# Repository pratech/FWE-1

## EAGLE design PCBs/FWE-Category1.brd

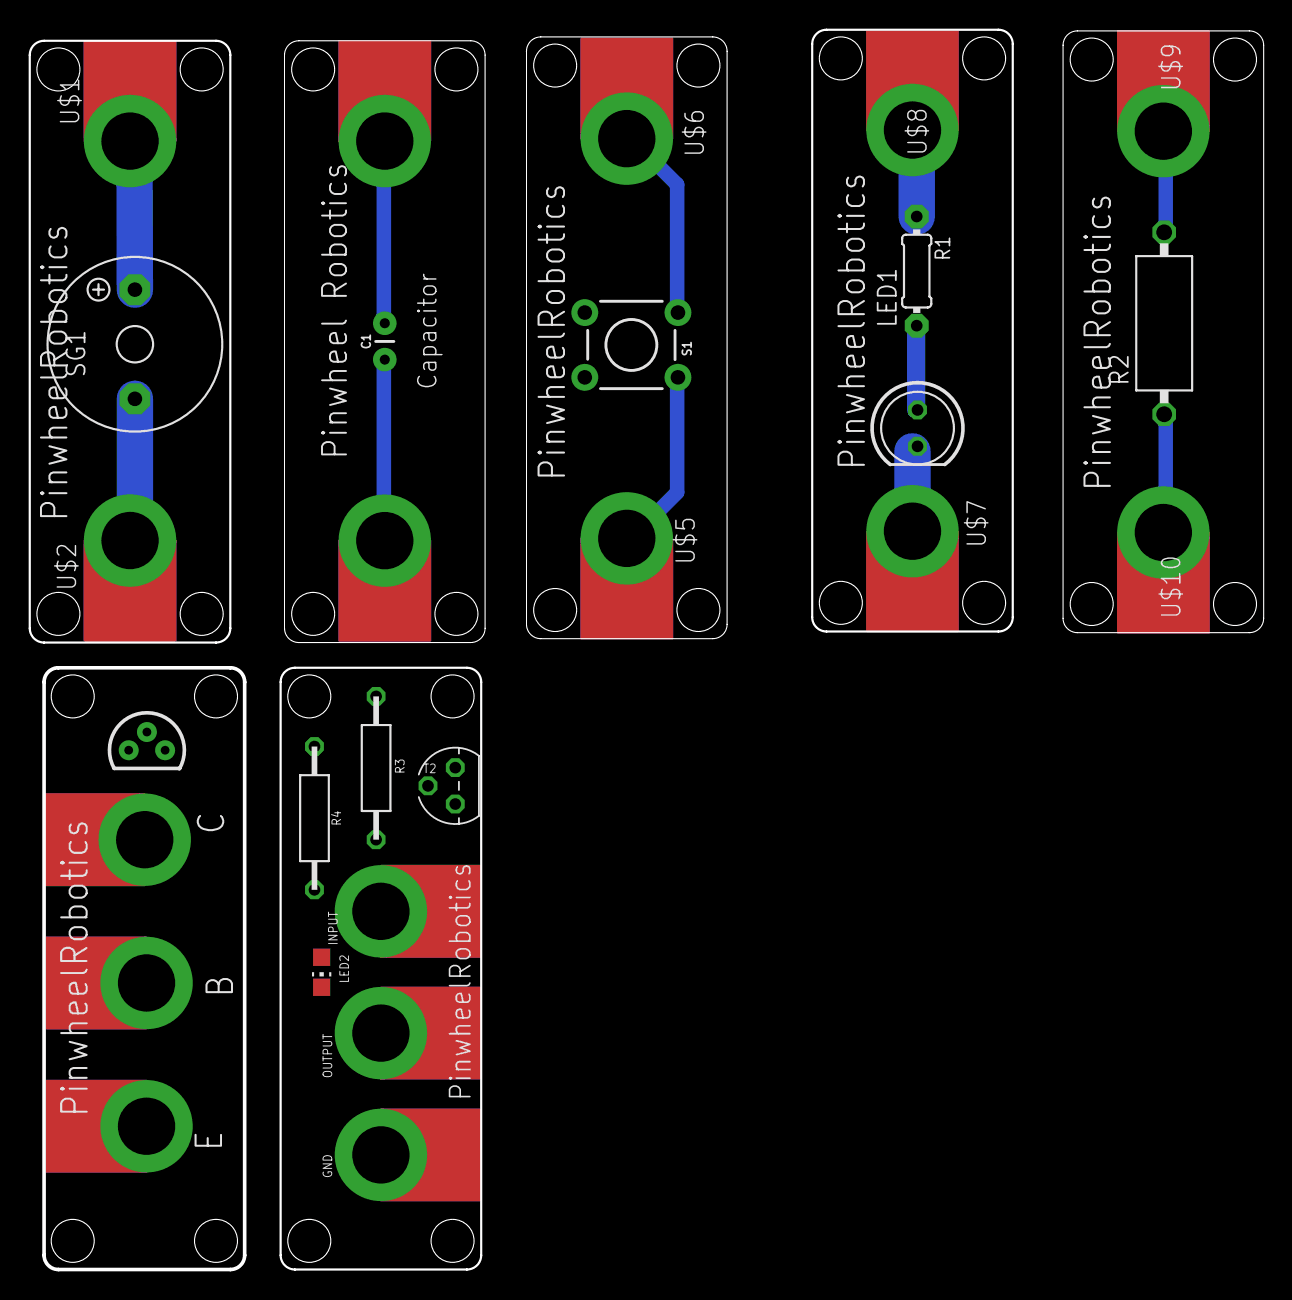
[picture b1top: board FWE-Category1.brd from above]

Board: 2 copper layers, 86.1 x 86.5 mm, 27 parts (0 on the bottom side), 19 nets.

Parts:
C1: 22pF; CAP-PTH-2.54
GND: MICROBIT_PAD
INPUT: MICROBIT_PAD
LED1: LED5MM
LED2: CHIP-LED0805
OUTPUT: MICROBIT_PAD
R1: 0204/7
R2: VMTB60
R3, R4: R0207/10
S1: MOMENTARY-SWITCH-SPST-PTH-6.0MM; TACTILE_SWITCH_PTH_6.0MM
SG1: F/TMB
T1: BC547N; TO92
T2: 2N3904; TO92
U$1, U$2, U$3, U$4, U$5, U$6, U$7, U$8, U$9, U$10, U$11, U$12, U$13: MICROBIT_PAD

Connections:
5V: INPUT.PAD, R3.1, R4.2
GND: GND.PAD, T2.3
unnamed: SG1.+, U$1.PAD
unnamed: SG1.-, U$2.PAD
unnamed: C1.1, U$4.PAD
unnamed: C1.2, U$3.PAD
unnamed: S1.1, U$5.PAD
unnamed: S1.3, U$6.PAD
unnamed: LED1.K, U$7.PAD
unnamed: LED1.A, R1.2
unnamed: R1.1, U$8.PAD
unnamed: R2.1, U$10.PAD
unnamed: R2.2, U$9.PAD
unnamed: T1.1, U$13.PAD
unnamed: T1.3, U$11.PAD
unnamed: LED2.A, R4.1
unnamed: LED2.C, OUTPUT.PAD, T2.1
unnamed: R3.2, T2.2
T1: T1.2, U$12.PAD

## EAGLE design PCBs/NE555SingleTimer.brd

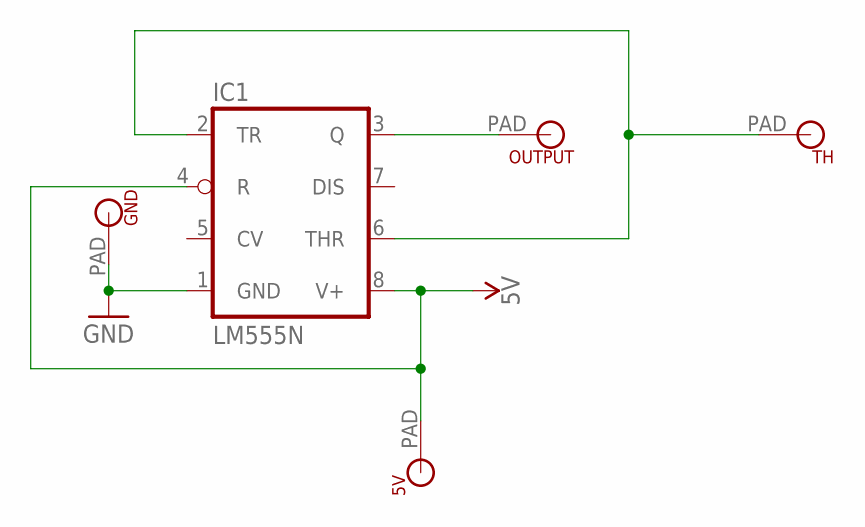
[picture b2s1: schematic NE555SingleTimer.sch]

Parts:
5V: MICROBIT_PAD
GND: MICROBIT_PAD
IC1: LM555N; DIL08
OUTPUT: MICROBIT_PAD
TH: MICROBIT_PAD

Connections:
5V: 5V.PAD, IC1.4 (R), IC1.8 (V+)
GND: GND.PAD, IC1.1 (GND)
unnamed: IC1.3 (Q), OUTPUT.PAD
unnamed: IC1.2 (TR), IC1.6 (THR), TH.PAD

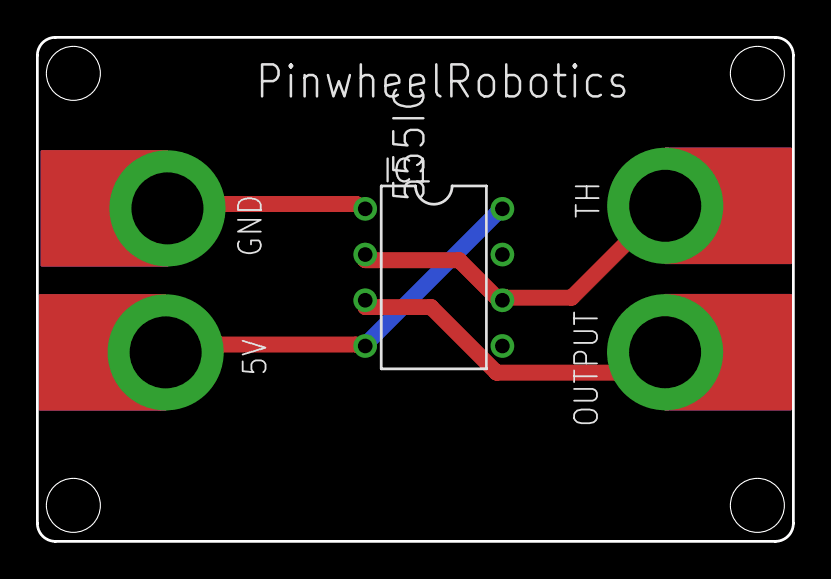
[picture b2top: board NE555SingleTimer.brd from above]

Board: 2 copper layers, 42.0 x 28.0 mm, 5 parts (0 on the bottom side), 4 nets.

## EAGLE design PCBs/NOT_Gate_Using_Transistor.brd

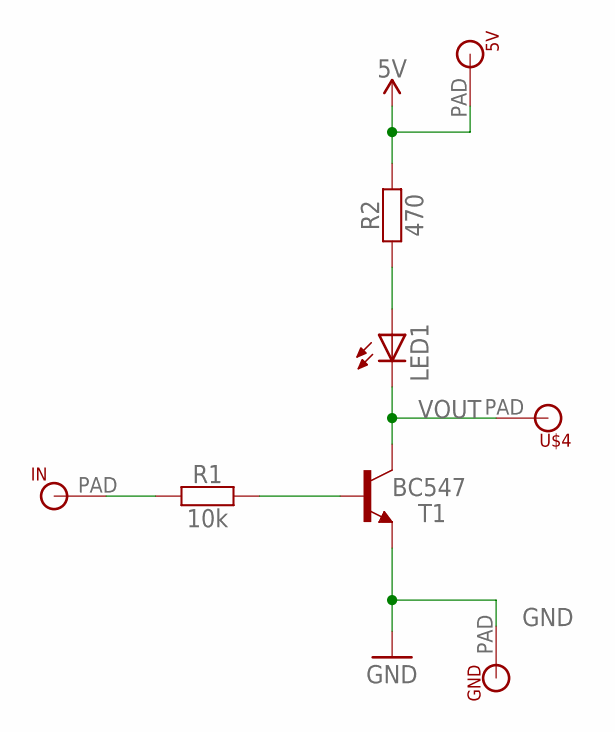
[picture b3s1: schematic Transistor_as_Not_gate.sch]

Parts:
5V: MICROBIT_PAD
GND: MICROBIT_PAD
IN: MICROBIT_PAD
LED1: LED3MM
R1: 10k; R0207/7
R2: 470; R0207/7
T1: BC547; TO92
U$4: MICROBIT_PAD

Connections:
5V: 5V.PAD, R2.2
GND: GND.PAD, T1.1 (E)
unnamed: R1.2, T1.2 (B)
unnamed: LED1.A, R2.1
unnamed: IN.PAD, R1.1
VOUT: LED1.K (C), T1.3 (C), U$4.PAD

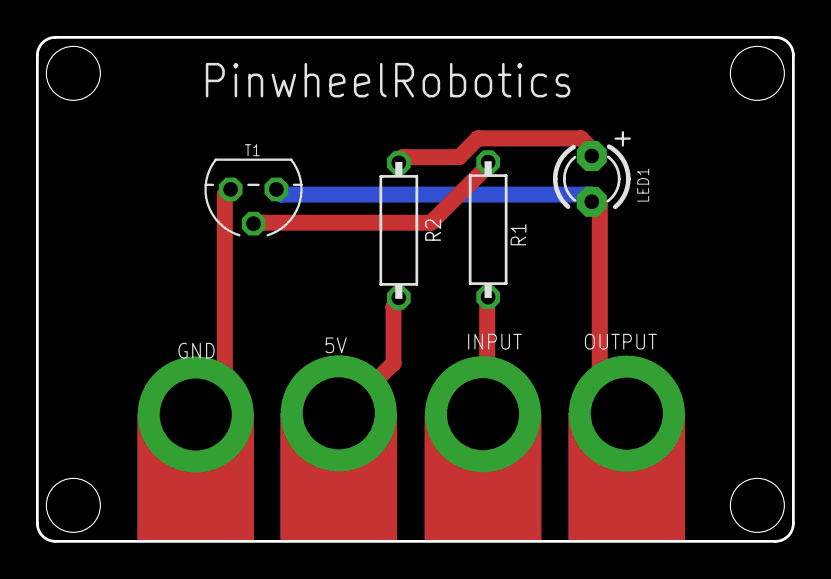
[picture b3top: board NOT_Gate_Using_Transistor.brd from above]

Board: 2 copper layers, 42.0 x 28.0 mm, 8 parts (0 on the bottom side), 6 nets.

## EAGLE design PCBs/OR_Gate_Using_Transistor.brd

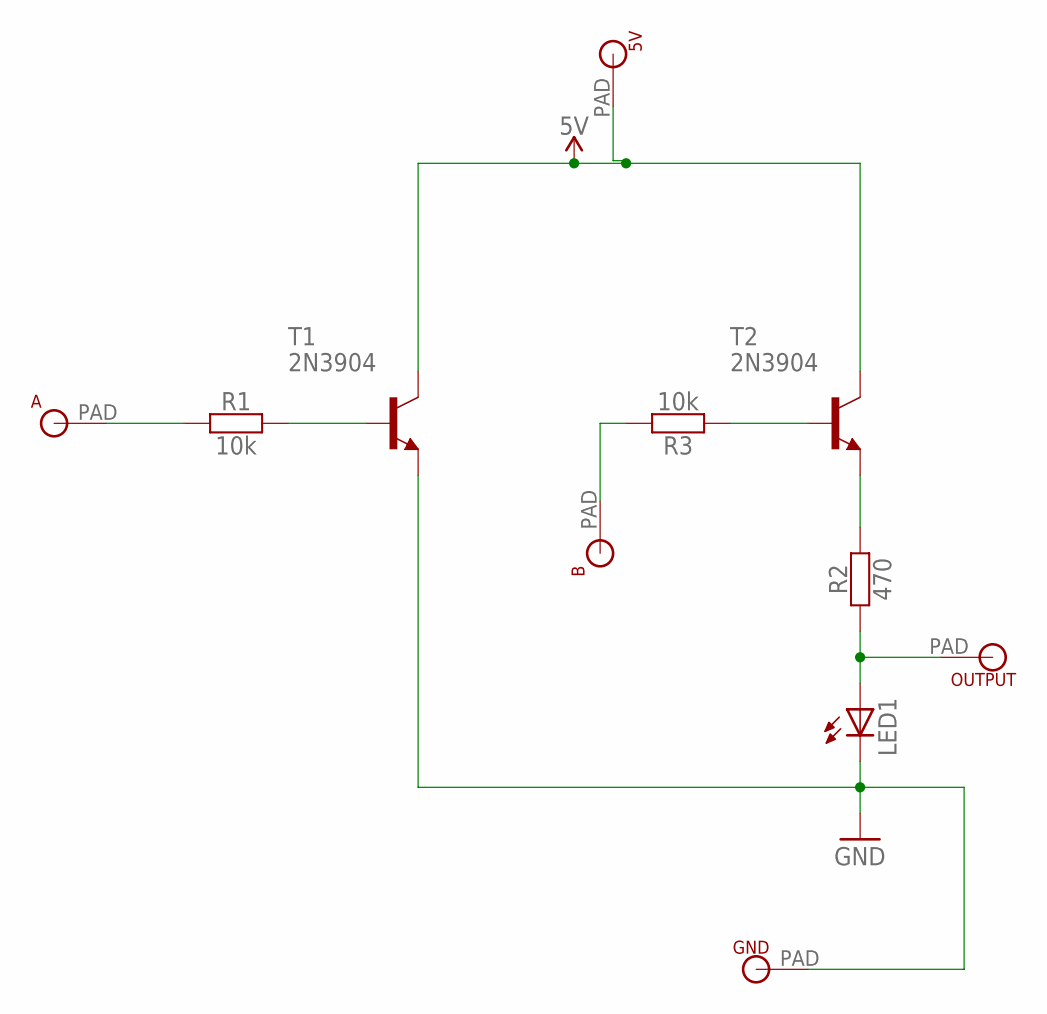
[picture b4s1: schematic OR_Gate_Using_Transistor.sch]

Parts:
5V: MICROBIT_PAD
A: MICROBIT_PAD
B: MICROBIT_PAD
GND: MICROBIT_PAD
LED1: LED3MM
OUTPUT: MICROBIT_PAD
R1, R3: 10k; R0207/7
R2: 470; R0207/7
T1, T2: 2N3904; TO92

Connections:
5V: 5V.PAD, T1.1 (C), T2.1 (C)
GND: GND.PAD, LED1.K (C), T1.3 (E)
unnamed: B.PAD, R3.2
unnamed: R3.1, T2.2 (B)
unnamed: R1.2, T1.2 (B)
unnamed: A.PAD, R1.1
unnamed: LED1.A, OUTPUT.PAD, R2.1
unnamed: R2.2, T2.3 (E)

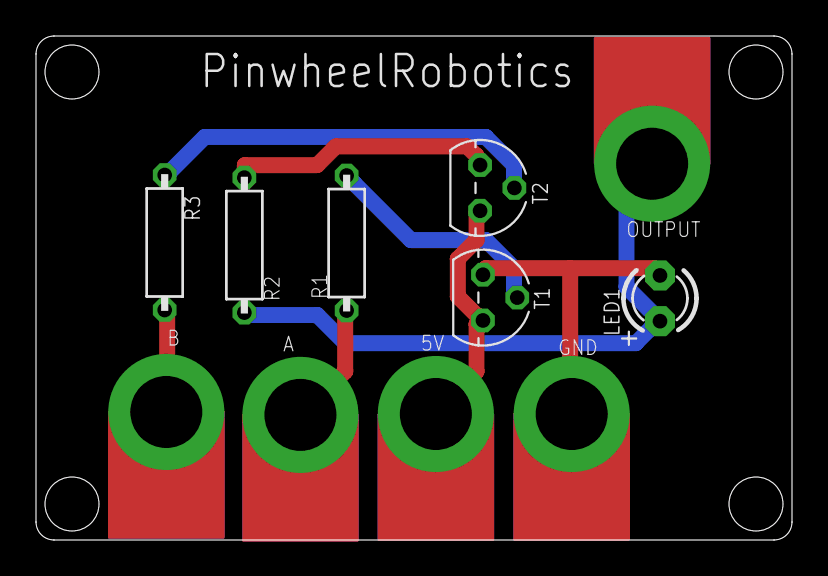
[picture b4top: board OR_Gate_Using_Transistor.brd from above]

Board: 2 copper layers, 42.0 x 28.0 mm, 11 parts (0 on the bottom side), 8 nets.

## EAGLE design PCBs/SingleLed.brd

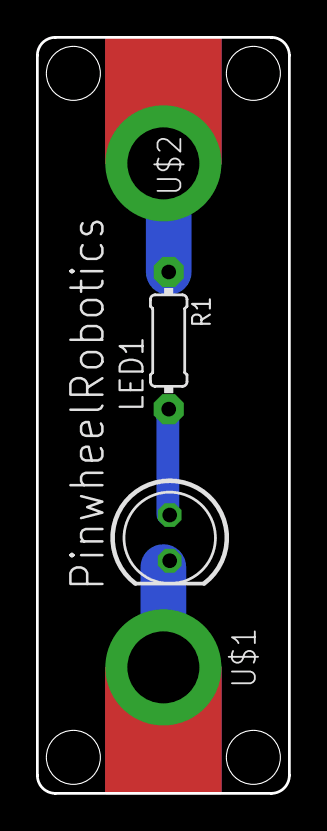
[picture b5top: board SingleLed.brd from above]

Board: 2 copper layers, 14.0 x 42.0 mm, 4 parts (0 on the bottom side), 3 nets.

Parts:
LED1: LED5MM
R1: 0204/7
U$1, U$2: MICROBIT_PAD

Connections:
unnamed: LED1.A, R1.2
unnamed: LED1.K, U$1.PAD
unnamed: R1.1, U$2.PAD

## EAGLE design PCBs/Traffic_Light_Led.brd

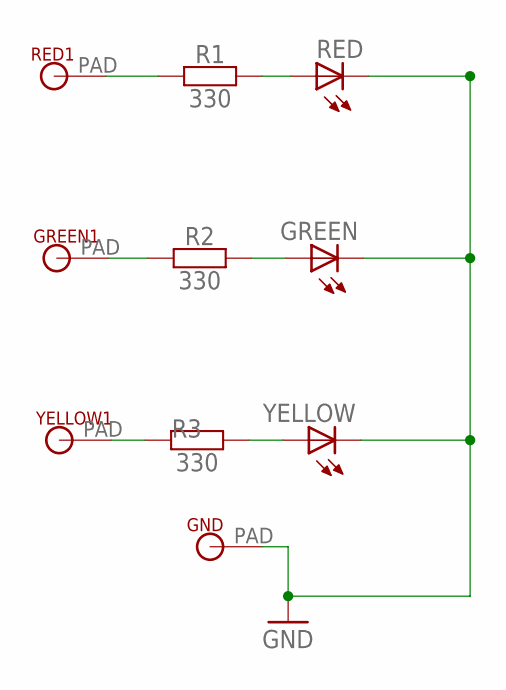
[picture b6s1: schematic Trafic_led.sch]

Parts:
GND: MICROBIT_PAD
GREEN: LED3MM
GREEN1: MICROBIT_PAD
R1, R2, R3: 330; R0207/7
RED: LED3MM
RED1: MICROBIT_PAD
YELLOW: LED3MM
YELLOW1: MICROBIT_PAD

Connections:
GND: GND.PAD, GREEN.K (C), RED.K (C), YELLOW.K (C)
unnamed: R1.1, RED1.PAD
unnamed: R3.1, YELLOW1.PAD
unnamed: GREEN.A, R2.2
unnamed: GREEN1.PAD, R2.1
unnamed: R3.2, YELLOW.A
unnamed: R1.2, RED.A

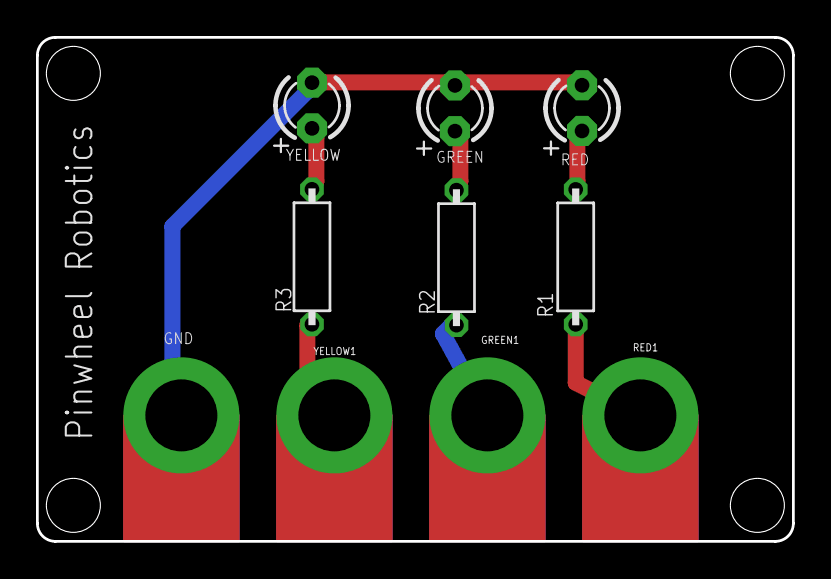
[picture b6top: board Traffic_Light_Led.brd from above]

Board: 2 copper layers, 42.0 x 28.0 mm, 10 parts (0 on the bottom side), 7 nets.

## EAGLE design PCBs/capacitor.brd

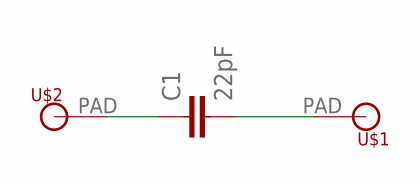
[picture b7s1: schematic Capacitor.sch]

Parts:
C1: 22pF; CAP-PTH-2.54
U$1, U$2: MICROBIT_PAD

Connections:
unnamed: C1.1, U$2.PAD
unnamed: C1.2, U$1.PAD

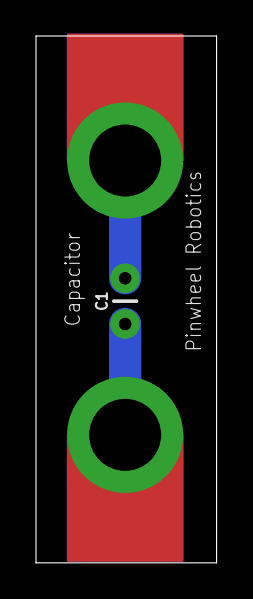
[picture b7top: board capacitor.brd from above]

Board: 2 copper layers, 10.0 x 29.3 mm, 3 parts (0 on the bottom side), 2 nets.

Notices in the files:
parts and their libraries:
SparkFun-Capacitors: Licensing: Creative Commons ShareAlike 4.0 International - https://creativecommons.org/licenses/by-sa/4.0
